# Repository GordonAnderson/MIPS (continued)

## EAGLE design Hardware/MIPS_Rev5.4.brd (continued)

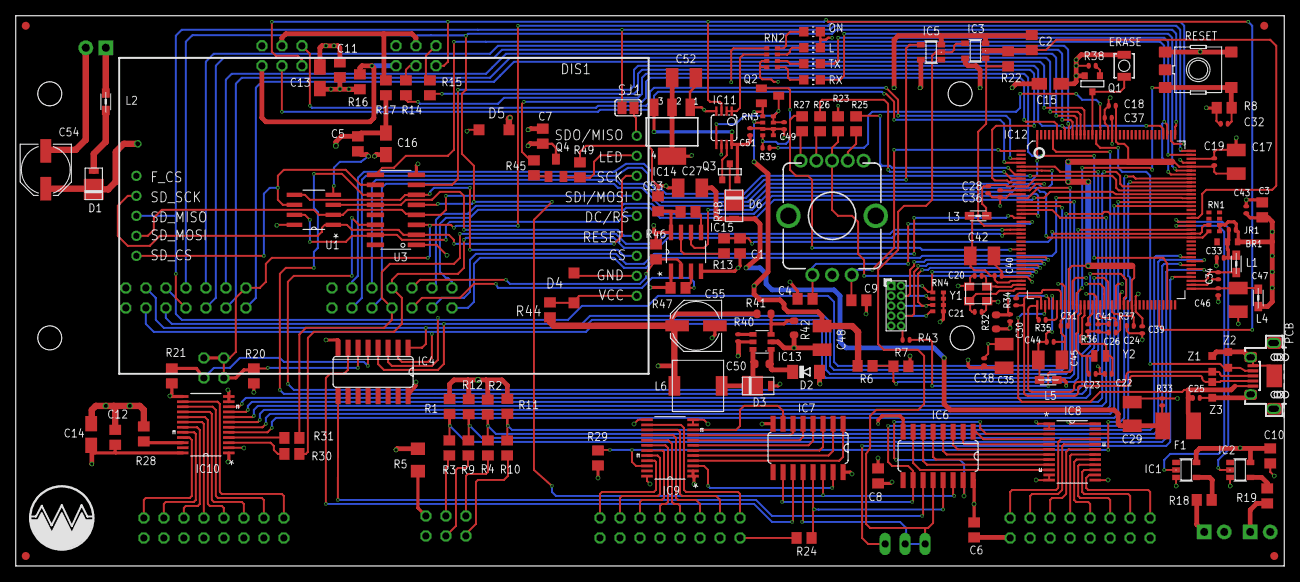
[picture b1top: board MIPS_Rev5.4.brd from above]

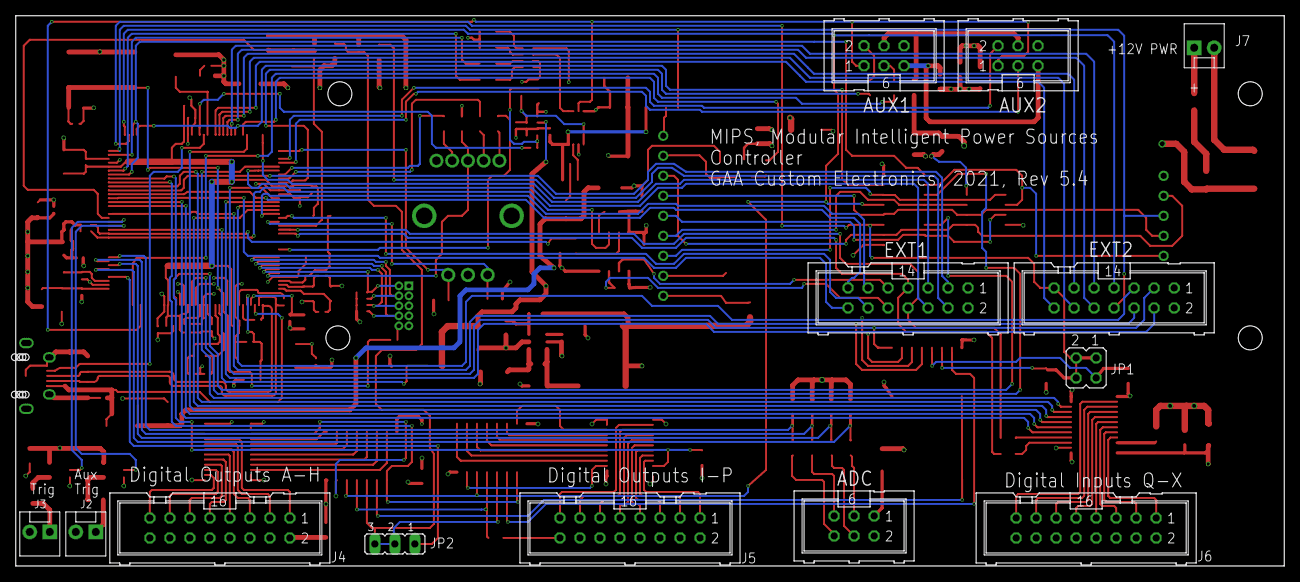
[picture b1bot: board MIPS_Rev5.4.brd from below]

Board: 4 copper layers, 161.0 x 69.8 mm, 178 parts (13 on the bottom side), 188 nets.

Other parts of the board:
U$1: LOGO2

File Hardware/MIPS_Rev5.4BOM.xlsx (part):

MIPS Controller, V5.4
Qty | Value | Device | Package | Part | Description | SUPPLIER | Part Number | Cost Each | Cost Total
1 | GREEN | LEDCHIP-LED0805 | CHIP-LED0805 | ON | LED GREEN DIFFUSED 0805 SMD | Digikey | 475-1410-1-ND | 0.25 | 0.25
3 | YELLOW | LEDCHIP-LED0805 | CHIP-LED0805 | L, RX, TX | LED YELLOW CLEAR 0805 SMD | Digikey | 160-1428-1-ND | 0.33 | 0.99
1 | 10pF | C-USC0805 | C0805 | C1 | 10pF, 50V, 0805 | Digikey | 709-1168-1-ND | 0.1 | 0.1
4 |  | CPOL-USA/3216-18R | A/3216-18R | C13, C14, C15, C16 | CAP TANT 10UF 10V 10% 1206 | Digikey | 399-3684-1-ND | 0.38 | 1.52
9 | 10u | CPOL-EUSMCB | SMC_B | C17, C27, C29, C35, C42, C45, C47, C48, C52 | CAP TANT 10UF 16V 20% 1411 | Digikey | 399-3708-1-ND | 0.51 | 4.59
19 | 100n | C-EUC0402 | C0402 | C18, C19, C24, C26, C28, C31, C33, C34, C36, C37, C38, C39, C40, C41, C43, C44,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 | CAP CER 0.1UF 16V X7R 0402 | Digikey | 445-4952-1-ND | 0.1 | 1.9000000000000001
1 | 1000pF | C-USC0805 | C0805 | C2 | 1000pF, 50V | Digikey | 399-1136-1-ND | 0.11 | 0.11
5 | 22p | C-EUC0402 | C0402 | C20, C21, C22, C23, C30 | CAP CER 22PF 10V C0G/NP0 0402 | Digikey | 732-7427-1-ND | 0.1 | 0.5
2 | 10n | C-EUC0402 | C0402 | C25, C32 | CAP CER 10000PF 16V X7R 0402 | Digikey | 478-3664-1-ND | 0.43 | 0.86
9 |  | C-USC0805 | C0805 | C3, C5, C6, C7, C8, C10, C11, C12, C53 | CAP CER 0.1UF 100V X7R 0805 | Digikey | 1276-2447-2-ND | 0.1 | 0.9
2 | 0.01uF | C-USC0805 | C0805 | C4, C9 | 0.01uF, 805 | Digikey | 399-1158-1-ND | 0.1 | 0.2
1 | 10n | C-EUC0603 | C0603-ROUND | C50 | CAP CER 10000PF 16V X7R 0603 | Digikey | 399-7841-1-ND | 0.33 | 0.33
2 | 100uF | CPOL-EUD | PANASONIC_D | C54, C55 | CAP ALUM 100UF 20% 25V SMD | Digikey | PCE3898CT-ND | 0.44 | 0.88
3 | SS1P3L | SS1P3L | DO220AAL | D1, D3, D6 | DIODE SCHOTTKY 30V 1.5A DO220AA | Digikey | SS1P3L-M3/84AGICT-ND | 0.48 | 1.44
1 | CD1206-S01575 | DIODE-MINIMELF | MINIMELF | D2 | DIODE SCHOTTKY 100V 1A 1206 | Digikey | 478-7807-1-ND | 0.16 | 0.16
1 | 5.1V | ZENER-DIODESOD123 | SOD123 | D4 | DIODE ZENER 5.1V 500MW SOD123 | Digikey | BZT52C5V1-TPMSCT-ND | 0.22 | 0.22
1 | 3.3V | ZENER-DIODESOD123 | SOD123 | D5 | DIODE ZENER 3.3V 500MW SOD123 | Digikey | MMSZ5226B-TPMSCT-ND | 0.21 | 0.21
1 | MF-MSMF050-2 500mA | L-EUL1812 | L1812 | F1 | PTC RESET FUSE 15V 500MA 1812 | Digikey | MF-MSMF050-2CT-ND | 0.66 | 0.66
1 | SP723ABG | SP723ABG | SOIC127P600X175-8N | U1 | TVS ARRAY ESD 6 INPUT 30V 8-SOIC | Digikey | F2721-ND | 2.86 | 2.86
1 | 74HC4050D | 74HC4050D | SOIC16 | U3 | IC BUFFER NON-INVERT 6V 16SOIC | Digikey | 74HC4050DCT-ND | 0.41 | 0.41
2 | 74AHC1G14DBV | 74AHC1G14DBV | SOT23-5 | IC1, IC2 | TinyLogic(R) UHS Inverter with Schmitt Trigger Input | Digikey | NC7SZ14M5XCT-ND | 0.45 | 0.9
1 | LMV358IDGKR | LMV358MMX | MSOP08 | IC11 | IC OPAMP GP 1MHZ RRO 8VSSOP | Digikey | 296-13455-1-ND | 0.8 | 0.8
1 | ATSAM3X8EA-AU | ATSAM3X/AAU | LQFP144 | IC12 | IC MCU 32BIT 512KB FLASH 144LQFP | Digikey | ATSAM3X8EA-AU-ND | 9.9700000000000006 | 9.9700000000000006
1 | LM2734Y | LM2736Y | SOT23-6 | IC13 | IC REG BUCK ADJ 1A TSOT23-6 | Digikey | LM2734YMK/NOPBCT-ND | 2.54 | 2.54
1 | NCP1117ST33T3G -3V3 | MC33269ST-3.3T3 | SOT223 | IC14 | IC REG LINEAR 3.3V 1A SOT223 | Digikey | NCP1117ST33T3GOSCT-ND | 0.47 | 0.47
1 | PCA9517D | PCA9517D | SOIC127P600X175-8N | IC15 | IC TRNSLTR BIDIRECTIONAL 8SOIC | Digikey | 296-39221-1-ND | 1.01 | 1.01
1 | 74AHC1G86DBV | 74AHC1G86DBV | SOT23-5 | IC3 | IC GATE XOR 1CH 2-INP SOT-23-5 | Digikey | 296-9853-1-ND | 0.4 | 0.4
1 | SN74HCT138DSOIC | SN74HCT138DSOIC | SO16 | IC4 | 3-LINE TO 8-LINE DECODERS /DEMULTIPLEXERXS | Digikey | 296-14863-1-ND | 0.49 | 0.49
1 | 74AHC1G04DBV | 74AHC1G04DBV | SOT23-5 | IC5 | IC SINGLE INVERTER-GATE SOT-23-5 | Digikey | 296-11599-1-ND | 0.49 | 0.49
2 | 74HC595D | 74HC595D | SO16 | IC6, IC7 | 8 BIT SHIFT REG 3ST-OUT 16SOIC | Digikey | 296-14857-1-ND | 0.59 | 1.18
3 | SN74LVCC3245APW | SN74LVCC3245APW | SOP65P640X120-24N | IC8, IC9, IC10 | IC BUS TRANSCEIVER 8BIT 24TSSOP | Digikey | 296-8564-1-ND | 1.26 | 3.7800000000000002
3 |  | ML6 | ML6 | ADC, AUX1, AUX2 | CONN HEADER R/A 6POS 2.54MM | Digikey | 609-2846-ND | 0.79 | 2.37
2 |  | ML14 | ML14 | EXT1, EXT2 | CONN HEADER R/A 14POS 2.54MM | Digikey | S9178-ND | 0.7 | 1.4
3 | M02POLAR | M02POLAR | MOLEX-1X2 | J2, J3, J7 | CONN HEADER VERT 2POS 2.54MM | Digikey | WM2700-ND | 0.46 | 1.3800000000000001
3 |  | ML16 | ML16 | J4, J5, J6 | CONN HEADER R/A 16POS 2.54MM | Digikey | S9179-ND | 0.73 | 2.19
1 | 2x2 | JP2QE | JP2Q | JP1 | Not installed
1 | 1x3 | JP2E | JP2 | JP2 | Not installed
1 |  | PINHEAD_PINHD-2X5PASSO127 | PINHEAD_2X05_127 | JTAG | Not installed
5 | MH2029-300Y | WE-CBF_0805 | 805 | L1, L2, L3, L4, L5 | FERRITE BEAD 30 OHM 0805 1LN | Digikey | MH2029-300YCT-ND | 0.1 | 0.5
1 | 10u SRR0604-100ML | L-USSRR0604 | SRR0604 | L6 | FIXED IND 10UH 1.3A 120 MOHM SMD | Digikey | SRR0604-100MLCT-ND | 0.8 | 0.8
2 | FDN340P | PMOSSOT23 | SOT-23 | Q1, Q3 | MOSFET P-CH 20V 2A SOT23-3L | Digikey | 785-1016-1-ND | 0.41 | 0.82
1 | BC847BSMD | BC847BSMD | SOT23 | Q2 | TRANS NPN 45V 0.1A SOT-23 | Digikey | BC847BLT3GOSCT-ND | 0.12 | 0.12
1 |  | MMBT2222ALT1-NPN-SOT23-BEC | SOT23-BEC | Q4 | NPN transistor | Digikey | MMBT2222ATPMSCT-ND | 0.14000000000000001 | 0.14000000000000001
9 | 10K | R-US_R0805 | R0805 | R1, R2, R3, R4, R6, R9, R10, R11, R12 | RES SMD 10K OHM 5% 1/8W 0805 | Digikey | P10KACT-ND | 0.1 | 0.9
2 | 10 | R-US_R0805 | R0805 | R13, R16 | RES SMD 10 OHM 1% 1/8W 0805 | Digikey | P10.0CCT-ND | 0.1 | 0.2
7 | 100 | R-US_R0805 | R0805 | R14, R15, R18, R19, R24, R30, R31 | RES SMD 100 OHM 5% 1/8W 0805 | Digikey | P100ACT-ND | 0.1 | 0.70000000000000007
2 | 1 | R-US_R0805 | R0805 | R17, R44 | RES SMD 1 OHM 5% 1/8W 0805 | Digikey | ERJ-6GEYJ1R0V | 0.1 | 0.2
3 | 330 | R-US_R0805 | R0805 | R25, R26, R27 | RES SMD 330 OHM 1% 1/8W 0805 | Digikey | P330CCT-ND | 0.1 | 0.30000000000000004
1 | 6k8 1% | R-EU_R0603 | R0603-ROUND | R32 | RES SMD 6.8K OHM 1% 1/10W 0603 | Digikey | P6.80KHCT-ND | 0.1 | 0.1
3 | 10K | R-EU_R0402 | R0402 | R33, R38, R40 | RES SMD 10K OHM 1% 1/10W 0402 | Digikey | P10.0KLCT-ND | 0.1 | 0.30000000000000004
2 | 39R 1% | R-EU_R0402 | R0402 | R34, R35 | RES SMD 39 OHM 1% 1/10W 0402 | Digikey | P39.0LCT-ND | 0.1 | 0.2
3 | 0R_NM | R-EU_R0402 | R0402 | JR1, R36, R43 | RES SMD 0 OHM JUMPER 1/10W 0402 | Digikey | P0.0JCT-ND | 0.1 | 0.30000000000000004
1 | 100K | R-EU_R0402 | R0402 | R37 | RES SMD 100K OHM 1% 1/10W 0402 | Digikey | P100KLCT-ND | 0.1 | 0.1
1 | 1K | R-EU_R0402 | R0402 | R39 | RES SMD 1K OHM 1% 1/10W 0402 | Digikey | P1.00KLCT-ND | 0.1 | 0.1
1 | 52K3 | R-EU_0603-RND | R0603-ROUND | R41 | RES SMD 52.3K OHM 1% 1/10W 0603 | Digikey | P52.3KHCT-ND | 0.1 | 0.1
1 | 10K | R-EU_0603-RND | R0603-ROUND | R42 | RES SMD 10K OHM 1% 1/10W 0603 | Digikey | P10.0KHCT-ND | 0.1 | 0.1
2 | 4700 | R-US_R0805 | R0805 | R46, R47 | RES SMD 4.7K OHM 5% 1/8W 0805 | Digikey | P4.7KACT-ND | 0.1 | 0.2
1 | 10 | R-US_R1206 | R1206 | R5 | RES SMD 10 OHM 5% 1/4W 1206 | Digikey | P10ECT-ND | 0.1 | 0.1
11 | 1K | R-US_R0805 | R0805 | R7, R8, R20, R21, R22, R23, R28, R29, R45, R48, R49 | RES SMD 1K OHM 5% 1/8W 0805 | Digikey | P1.0KACT-ND | 0.1 | 1.1000000000000001
1 | 1K5 | 4R-NCAT16 | CAT16 | RN1 | RES ARRAY 4 RES 1.5K OHM 1206 | Digikey | YC164J-1.5KCT-ND | 0.1 | 0.1
1 | 1k | 4R-NCAY16 | CAY16 | RN2 | RES ARRAY 4 RES 1K OHM 1206 | Digikey | YC164J-1.0KCT-ND | 0.1 | 0.1
2 | 100K | 4R-NCAT16 | CAT16 | RN3, RN4 | RES ARRAY 4 RES 100K OHM 1206 | Digikey | YC164J-100KCT-ND | 0.1 | 0.2
1 |  | ENCODER_RGB_CA | ENCODER_LED_3 | SW1 | ROTARY ENCODER MECHANICAL 24PPR | Digikey | PEL12T-4225S-S1024-ND | 5.5 | 5.5
1 | B3U | B3U | B3U | ERASE | SWITCH TACTILE SPST-NO 0.05A 12V | Digikey | SW1143CT-ND | 0.92 | 0.92
1 | TS42 | TS42 | TS42 | RESET | SWITCH TACTILE SPST-NO 0.05A 12V | Digikey | CKN9084CT-ND | 0.19 | 0.19
1 | MICRO-USB-AB1 | MICRO_USB | MCR-AB1-S-RA-SMT | USB1 | CONN RCPT MICRO USB AB R/A SMD | Digikey | WM17143CT-ND | 0.83 | 0.83
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
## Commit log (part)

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2015-07-01 MIPS arduino code
    The is the source code for the MIPS system. This source requires the
    libraries in the MIPSlib repository
2015-12-07 V1.21 update
    Added support to ARB module and Filament module. Lots of minor bug
    fixes. Also added support for WiFi connection when using a ESP8266
    module.
2016-01-26 V1.27
    Upgraded Filament module to support cycling. Added support for two
    Twave modules and rev 3.0 of Twave, also added compressor support.
2016-05-03 Version 1.42
    Commit version 1.42 updates
2016-05-22 V1.47
    Upgrades to support Twave compressors new features.
2016-06-24 Rev 1.50 updates
    June 23 2016
2016-08-19 V1.59 updated
    Lots of big fixes and feature additions.
2016-12-16 Version 1.72
    Updates to a number of modules and addition of the High Order FAIMS
    module. Many small bug fixes.
2017-03-15 Upgrade to 1.79
    New version submit
2017-07-31 Version 1.92
2018-02-19 Feb 2018 update
2018-06-29 Update to version 1.127, June 2018
2018-07-29 V1.133 commit
2018-08-11 August 11, 2018
2018-08-25 Aug 25, 2018
2018-09-29 Sept 2018 update
2018-10-04 oct 3, 2018
2018-11-02 Nov 2, 2018 update
2018-12-08 Dec 7, 2018
2018-12-31 Dec 30, 2018
2019-01-07 1/6/2019
2019-01-18 Jan 18, 2019 update
2019-01-25 Jan 25, 2019 update
2019-02-11 Feb 11, 2019 updates
2019-02-17 Feb 17, 2019 update
2019-02-25 Feb 25, 2019
2019-05-15 May 14, 2019
2019-05-27 Version 1.154
2019-07-25 July 24, 2019 update
2019-11-14 Nov 14, 2019
2020-03-28 MIPS 1.174
    March 28, 2020 update
2020-09-30 Sept 30, 2020
    Rev 1.188.
2021-03-08 V1.200 update
2021-05-02 05/02/2021
    Added calibration functions, MIPS logging, RTC, and FAIMS module updates
2021-06-01 June 1, 2021
2021-09-17 Sept 16, 2021
2024-12-07 Rev 1.249
2024-12-08 Update
    Added hardware folder and documentation
2026-04-12 Removed warnings
2026-04-12 Added build version and variant message
2026-04-12 Added todo list, docs, and command file build
2026-04-13 Fixed CPUTEMP bug, updated USB id inforation
2026-04-13 Updated todo, fixed CPUTEMP bug, Updated USB id information
2026-05-15 Fixed pointer bug in SaveRF2EEPROM
2026-05-25 RFdriver gate minor bug
2026-05-25 Fixed RFdriver GUI update bug
2026-06-21 HVPS driver updates
2026-06-21 Added ADC control for HVPS and ESI
2026-06-23 Added comments
2026-06-23 added DAC cal parameter get/set
2026-06-24 Added rounding to ADC control
2026-06-24 Code cleanup
2026-06-24 ADC control bug fixes
2026-06-25 minor updates
2026-06-25 Added comments
2026-06-30 Add handling for zero voltage in ESI module calibration
